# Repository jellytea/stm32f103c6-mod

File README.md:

# stm32f103c6-mod
STM32F103C6 Core Board

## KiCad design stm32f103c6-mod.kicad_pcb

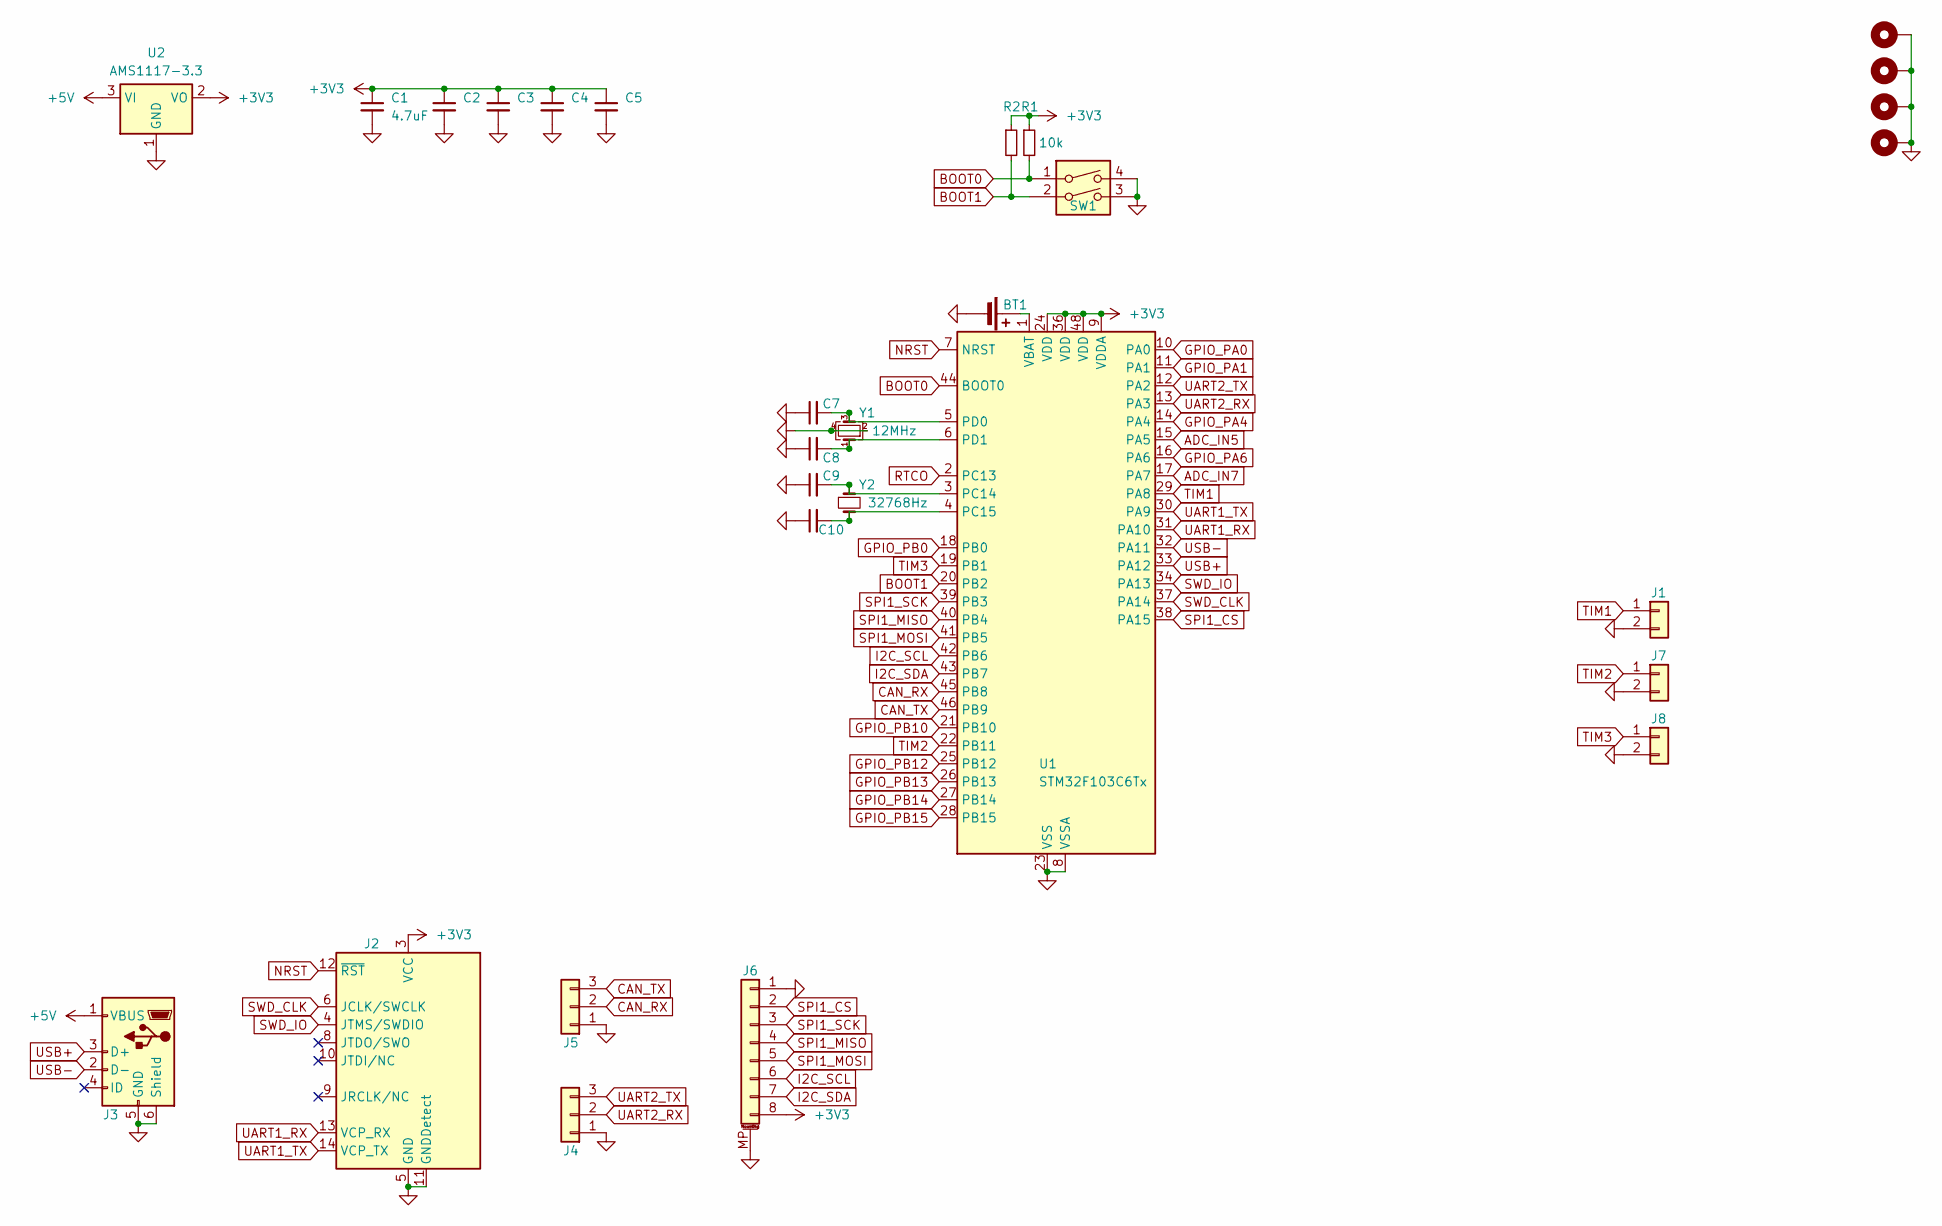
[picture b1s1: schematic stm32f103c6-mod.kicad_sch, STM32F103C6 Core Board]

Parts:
BT1: Battery_Cell; PinHeader_1x02_P1.00mm_Vertical
C1, C2, C3, C4, C5: 4.7uF; C_0603_1608Metric
C7, C8, C9, C10: 10pF; C_0603_1608Metric
H1, H2, H3, H4: MountingHole_Pad; MountingHole_2.7mm_Pad_Via
J1, J7, J8: Conn_01x02; PinHeader_1x02_P2.54mm_Horizontal
J2: Conn_ST_STDC14; PinHeader_2x07_P1.27mm_Vertical_SMD
J3: USB_B_Micro; USB_Micro-B_Amphenol_10118194_Horizontal
J4, J5: Conn_01x03; PinHeader_1x03_P2.54mm_Horizontal
J6: Conn_01x08_MountingPin; TE_84952-8_1x08-1MP_P1.0mm_Horizontal
R1, R2: 10k; R_0603_1608Metric
SW1: SW_DIP_x02; SW_DIP_SPSTx02_Slide_Copal_CHS-02B_W7.62mm_P1.27mm
U1: STM32F103C6Tx; LQFP-48_7x7mm_P0.5mm
U2: AMS1117-3.3; SOT-223-3_TabPin2
Y1: 12MHz; Crystal_SMD_3225-4Pin_3.2x2.5mm
Y2: 32768Hz; Crystal_SMD_3215-2Pin_3.2x1.5mm

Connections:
+3V3: C1.1, C2.1, C3.1, C4.1, C5.1, J2.3 (VCC), J6.8, R1.1, R2.1, U1.9 (VDDA), U1.24 (VDD), U1.36 (VDD), U1.48 (VDD), U2.2 (VO)
+5V: J3.1 (VBUS), U2.3 (VI)
ADC_IN5: U1.15 (PA5)
ADC_IN7: U1.17 (PA7)
BOOT0: R1.2, SW1.1, U1.44 (BOOT0)
BOOT1: R2.2, SW1.2, U1.20 (PB2)
CAN_RX: J5.2, U1.45 (PB8)
CAN_TX: J5.3, U1.46 (PB9)
GND: BT1.2 (-), C1.2, C2.2, C3.2, C4.2, C5.2, C7.1, C8.1, C9.1, C10.1, H1.1, H2.1, H3.1, H4.1, J1.2, J2.5 (GND), J2.7 (GND), J2.11 (GNDDetect), J3.5 (GND), J3.6 (Shield), J4.1, J5.1, J6.1, J6.MP (MountPin), J7.2, J8.2, SW1.3, SW1.4, U1.8 (VSSA), U1.23 (VSS), U1.35 (VSS), U1.47 (VSS), U2.1 (GND), Y1.2, Y1.4
GPIO_PA0: U1.10 (PA0)
GPIO_PA1: U1.11 (PA1)
GPIO_PA4: U1.14 (PA4)
GPIO_PA6: U1.16 (PA6)
GPIO_PB0: U1.18 (PB0)
GPIO_PB10: U1.21 (PB10)
GPIO_PB12: U1.25 (PB12)
GPIO_PB13: U1.26 (PB13)
GPIO_PB14: U1.27 (PB14)
GPIO_PB15: U1.28 (PB15)
I2C_SCL: J6.6, U1.42 (PB6)
I2C_SDA: J6.7, U1.43 (PB7)
NRST: J2.12 (~RST), U1.7 (NRST)
unnamed: BT1.1 (+), U1.1 (VBAT)
unnamed: C9.2, U1.3 (PC14), Y2.1
unnamed: C10.2, U1.4 (PC15), Y2.2
unnamed: C7.2, U1.5 (PD0), Y1.3
unnamed: C8.2, U1.6 (PD1), Y1.1
RTCO: U1.2 (PC13)
SPI1_CS: J6.2, U1.38 (PA15)
SPI1_MISO: J6.4, U1.40 (PB4)
SPI1_MOSI: J6.5, U1.41 (PB5)
SPI1_SCK: J6.3, U1.39 (PB3)
SWD_CLK: J2.6 (JCLK/SWCLK), U1.37 (PA14)
SWD_IO: J2.4 (JTMS/SWDIO), U1.34 (PA13)
TIM1: J1.1, U1.29 (PA8)
TIM2: J7.1, U1.22 (PB11)
TIM3: J8.1, U1.19 (PB1)
UART1_RX: J2.13 (VCP_RX), U1.31 (PA10)
UART1_TX: J2.14 (VCP_TX), U1.30 (PA9)
UART2_RX: J4.2, U1.13 (PA3)
UART2_TX: J4.3, U1.12 (PA2)
USB+: J3.3 (D+), U1.33 (PA12)
USB-: J3.2 (D-), U1.32 (PA11)

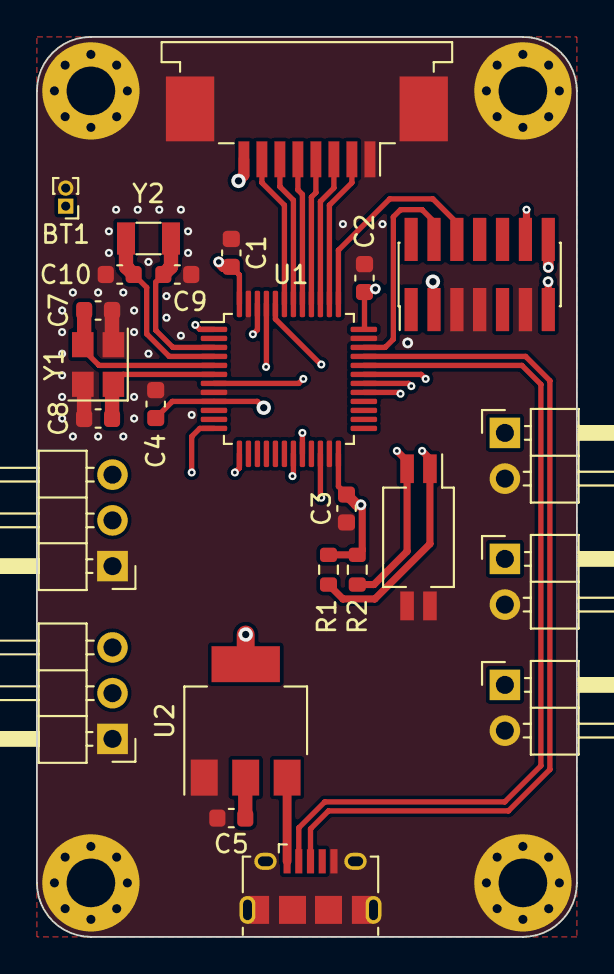
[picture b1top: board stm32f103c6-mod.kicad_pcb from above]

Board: 4 copper layers, 30.0 x 50.0 mm, 29 parts (0 on the bottom side), 30 nets.

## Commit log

2023-12-30 Revision 1.0

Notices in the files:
stm32f103c6-mod.kicad_pcb:
https://creativecommons.org/licenses/by-sa/4.0/legalcode.en
Use of this PCB design is governed under the CC BY-SA 4.0 International license.
stm32f103c6-mod.kicad_sch:
Use of this schematic is governed under the CC BY-SA 4.0 International license.
